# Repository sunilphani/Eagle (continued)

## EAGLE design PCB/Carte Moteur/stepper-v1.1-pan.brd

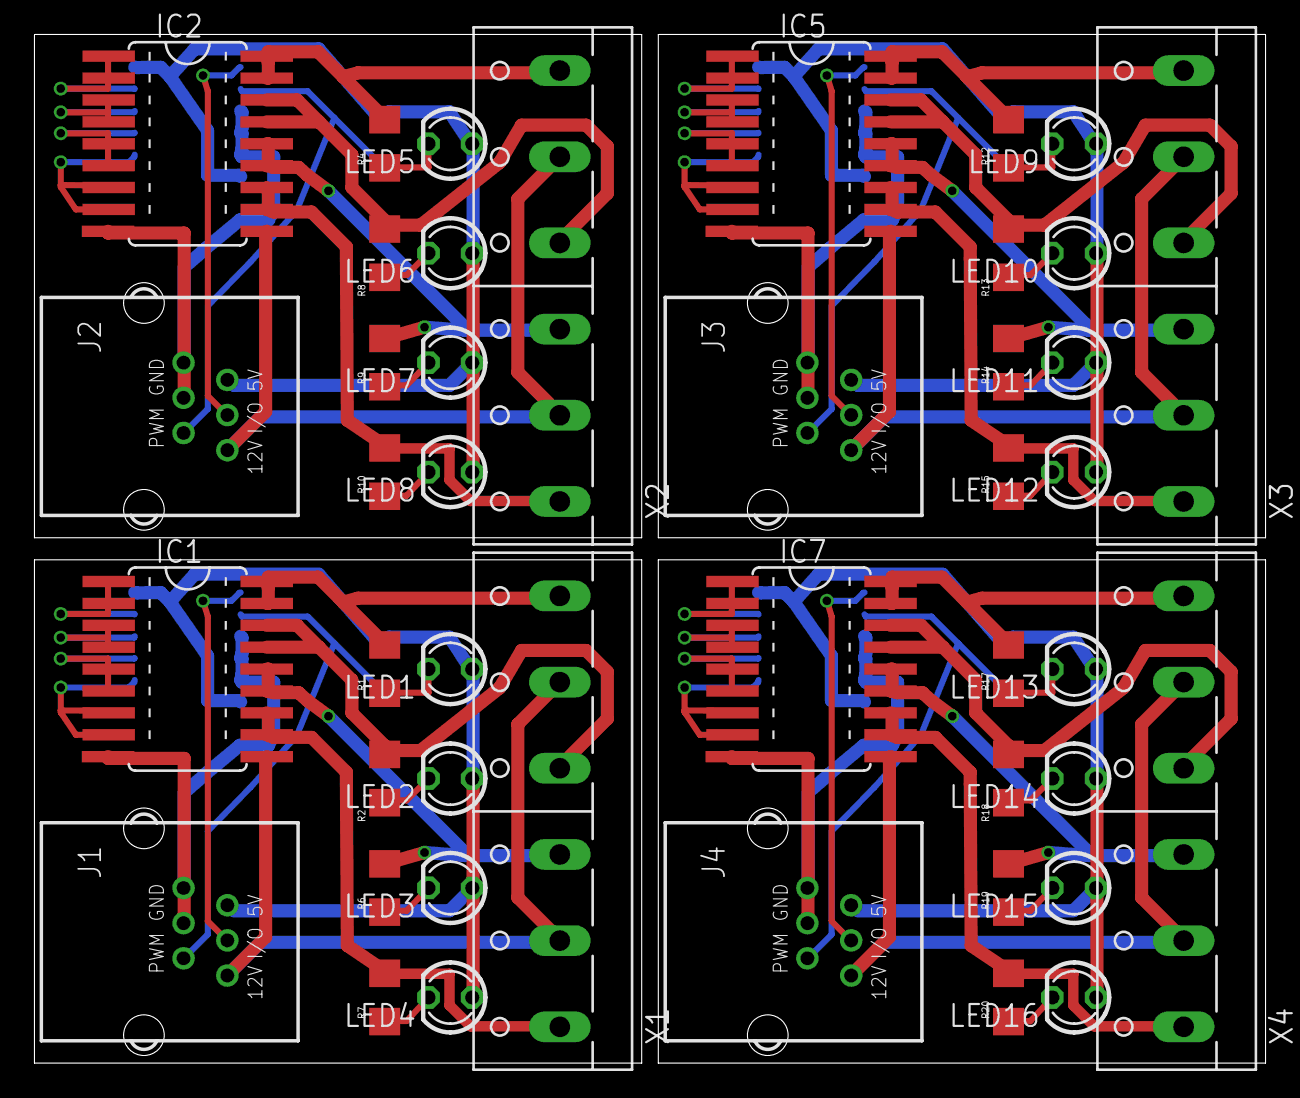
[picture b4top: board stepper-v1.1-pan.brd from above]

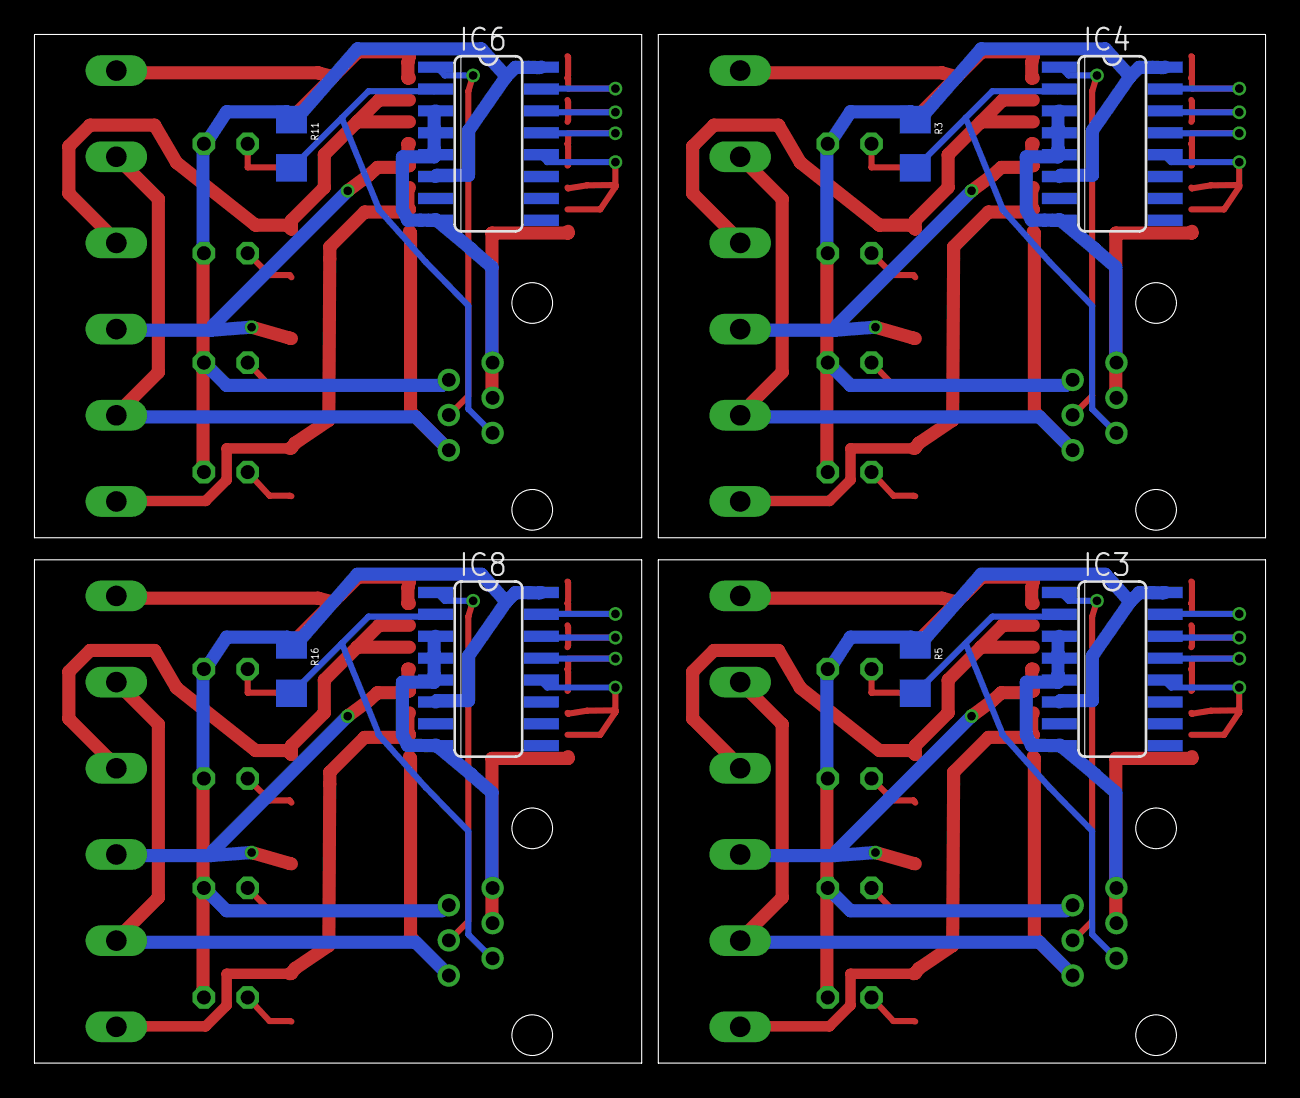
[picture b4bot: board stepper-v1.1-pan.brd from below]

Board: 2 copper layers, 71.4 x 59.7 mm, 52 parts (8 on the bottom side), 68 nets.

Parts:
IC1, IC2, IC5, IC7: ULN2803; SO18W
IC3, IC4, IC6, IC8: CD74HC238M; SO16
J1, J2, J3, J4: RJ12RIGHTANGLE; RJ12-RIGHTANGLE
LED1, LED2, LED3, LED4, LED5, LED6, LED7, LED8, LED9, LED10, LED11, LED12, LED13, LED14, LED15, LED16: LED3MM
R1, R2, R3, R4, R5, R6, R7, R8, R9, R10, R11, R12, R13, R14, R15, R16, R17, R18, R19, R20: 1k; 1206
X1, X2, X3, X4: W237-6

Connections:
+5V: IC3.6, IC3.16, J1.+5V, LED1.A, LED2.A, LED3.A, LED4.A, R5.1
+5V1: IC4.6, IC4.16, J2.+5V, LED5.A, LED6.A, LED7.A, LED8.A, R3.1
+5V2: IC6.6, IC6.16, J3.+5V, LED9.A, LED10.A, LED11.A, LED12.A, R11.1
+5V3: IC8.6, IC8.16, J4.+5V, LED13.A, LED14.A, LED15.A, LED16.A, R16.1
+12V: IC1.10, J1.+12V, X1.2, X1.5
+12V1: IC2.10, J2.+12V, X2.2, X2.5
+12V2: IC5.10, J3.+12V, X3.2, X3.5
+12V3: IC7.10, J4.+12V, X4.2, X4.5
GND: IC1.9, IC3.3, IC3.4, IC3.5, IC3.8, J1.GND1, J1.GND2
GND1: IC2.9, IC4.3, IC4.4, IC4.5, IC4.8, J2.GND1, J2.GND2
GND2: IC5.9, IC6.3, IC6.4, IC6.5, IC6.8, J3.GND1, J3.GND2
GND3: IC7.9, IC8.3, IC8.4, IC8.5, IC8.8, J4.GND1, J4.GND2
unnamed: IC1.1, IC1.2, IC3.15
unnamed: IC3.2, J1.PWM, R5.2
unnamed: IC1.17, IC1.18, R1.2, X1.6
unnamed: IC1.15, IC1.16, R2.2, X1.4
unnamed: IC1.13, IC1.14, R6.2, X1.3
unnamed: IC1.11, IC1.12, R7.2, X1.1
unnamed: IC1.7, IC1.8, IC3.12
unnamed: IC1.3, IC1.4, IC3.14
unnamed: LED1.K, R1.1
unnamed: LED2.K, R2.1
unnamed: LED3.K, R6.1
unnamed: LED4.K, R7.1
unnamed: IC3.1, J1.I/O
unnamed: IC1.5, IC1.6, IC3.13
unnamed: IC2.1, IC2.2, IC4.15
unnamed: IC4.2, J2.PWM, R3.2
unnamed: IC2.17, IC2.18, R4.2, X2.6
unnamed: IC2.15, IC2.16, R8.2, X2.4
unnamed: IC2.13, IC2.14, R9.2, X2.3
unnamed: IC2.11, IC2.12, R10.2, X2.1
unnamed: IC2.5, IC2.6, IC4.13
unnamed: IC2.7, IC2.8, IC4.12
unnamed: LED5.K, R4.1
unnamed: LED6.K, R8.1
unnamed: LED7.K, R9.1
unnamed: LED8.K, R10.1
unnamed: IC2.3, IC2.4, IC4.14
unnamed: IC4.1, J2.I/O
unnamed: IC5.1, IC5.2, IC6.15
unnamed: IC6.2, J3.PWM, R11.2
unnamed: IC5.17, IC5.18, R12.2, X3.6
unnamed: IC5.15, IC5.16, R13.2, X3.4
unnamed: IC5.13, IC5.14, R14.2, X3.3
unnamed: IC5.11, IC5.12, R15.2, X3.1
unnamed: IC5.5, IC5.6, IC6.13
unnamed: IC5.7, IC5.8, IC6.12
unnamed: LED9.K, R12.1
unnamed: LED10.K, R13.1
unnamed: LED11.K, R14.1
unnamed: LED12.K, R15.1
unnamed: IC5.3, IC5.4, IC6.14
unnamed: IC6.1, J3.I/O
unnamed: IC7.1, IC7.2, IC8.15
unnamed: IC8.2, J4.PWM, R16.2
unnamed: IC7.17, IC7.18, R17.2, X4.6
unnamed: IC7.15, IC7.16, R18.2, X4.4
unnamed: IC7.13, IC7.14, R19.2, X4.3
unnamed: IC7.11, IC7.12, R20.2, X4.1
unnamed: IC7.5, IC7.6, IC8.13
unnamed: IC7.7, IC7.8, IC8.12
unnamed: LED13.K, R17.1
unnamed: LED14.K, R18.1
unnamed: LED15.K, R19.1
unnamed: LED16.K, R20.1
unnamed: IC7.3, IC7.4, IC8.14
unnamed: IC8.1, J4.I/O

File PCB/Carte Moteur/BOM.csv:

"Qty";"Value";"Device";"Package";"Parts";"Description";"";
"1";"";"W237-6";"W237-6";"X1";"WAGO SCREW CLAMP";"";
"5";"1k";"RESISTOR1206";"1206";"R1, R2, R5, R6, R7";"Resistor";"";
"1";"CD74HC238M";"74238D";"SO16";"IC3";"3 to 8 line DECODER/DEMULTIPLEXER";"";
"4";"LED3MM";"LED3MM";"LED3MM";"LED1, LED2, LED3, LED4";"";"";
"1";"RJ12RIGHTANGLE";"RJ12RIGHTANGLE";"RJ12-RIGHTANGLE";"J1";"CORCOM Modular RJ Jacks No Shield";"";
"1";"ULN2803";"ULN2803A";"SO18W";"IC1";"DRIVER ARRAY";"";
